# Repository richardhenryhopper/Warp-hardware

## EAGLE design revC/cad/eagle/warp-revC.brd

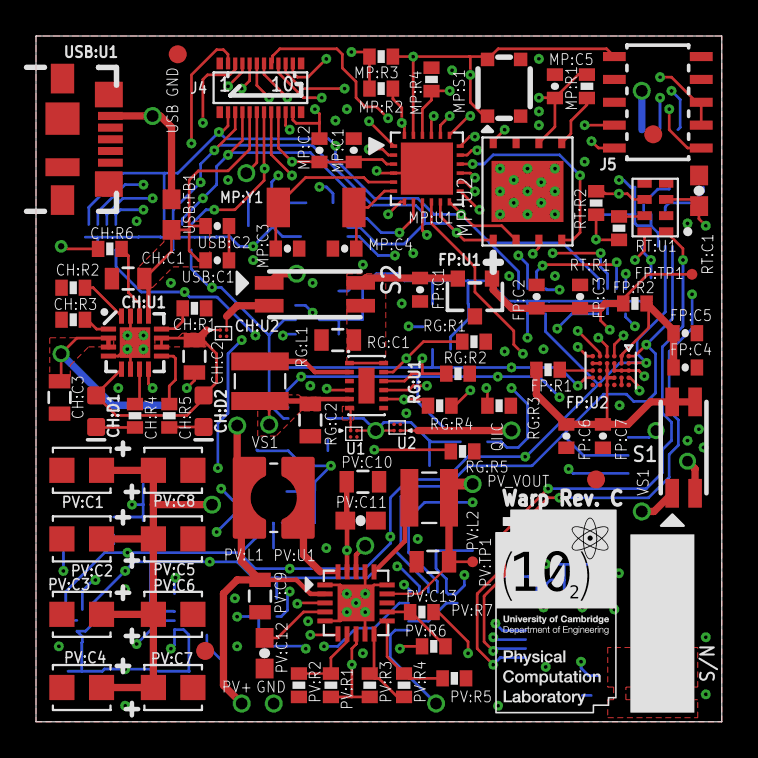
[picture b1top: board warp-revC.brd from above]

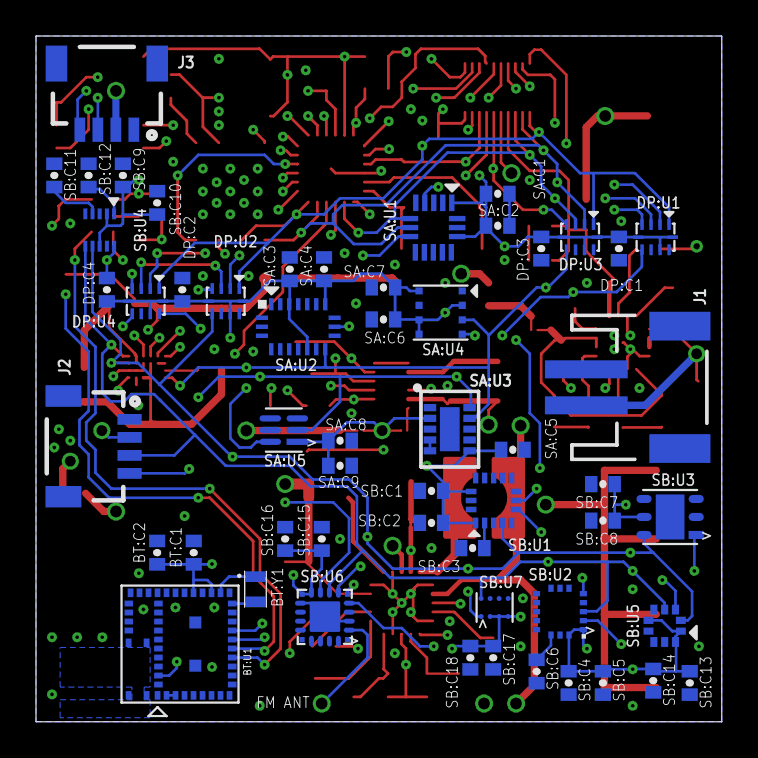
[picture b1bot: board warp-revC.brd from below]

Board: 10 copper layers, 38.1 x 38.1 mm, 143 parts (54 on the bottom side), 72 nets.

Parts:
BT:C1: 0.1uF; 0402-CAP
BT:C2: 1uF; 0402-CAP
BT:U1: BGX13S22GA-V21R; BGX13S
BT:Y1: IQXC-25
CH:C1: 1uF; 0805
CH:C2, CH:C3: 4.7uF; 0805
CH:D1, CH:D2: LED-0603
CH:R1: 2.94k; 0402-RES
CH:R2: 4.32k; 0402-RES
CH:R3: 10k; 0402-RES
CH:R4, CH:R5: 4.7k; 0402-RES
CH:R6: 56.2k; 0402-RES
CH:U1: BQ24230VQFN; PVQFN-N16
CH:U2: MAX40200; DSBGA
DP:C1, DP:C2, DP:C3, DP:C4: 0.1uF; 0402-CAP
DP:U1, DP:U2, DP:U3, DP:U4: ISL23415UTQFN; ISL23415
FD1, FD2, FD3, FD4: FIDUCIAL1X2; FIDUCIAL-1X2
FP:C1, FP:C2: 1uF; 0402-CAP
FP:C3, FP:C4, FP:C7: 0.1uF; 0402-CAP
FP:C5, FP:C6: 10uF; 0402-CAP
FP:R1: 10k; 0402-RES
FP:R2: 100; 0402-RES
FP:TP1: TPSTP06R; TP06R
FP:U1: MCP1811AT-012/TTSOT-23-3; SOT23-3
FP:U2: ICE40UP5K-UWG30; LATTICE-WLCSP-30
J1: JST-2-SMD
J2, J3: QIIC connector; 1X04_1MM_RA
J4: DF40FC-20DP-0.4V(51); DF40C-20DP-0.4V(51)
J5: CORTEX_DEBUG_SMD; SAMTECH_FTSH-105-01
MP:C1, MP:C5: 0.1uF; 0402-CAP
MP:C2: 4.7uF (pol); 0402-CAP
MP:C3, MP:C4: 33pF; 0402-CAP
MP:R1, MP:R2, MP:R4: 10k; 0402-RES
MP:R3: 4.7k; 0402-RES
MP:S1: EVPAYG0BAEVPAYG0BA; EVPAYG0BA
MP:U1: MKL03Z32VFK4RQFN24; MKL03Z32VFK4R
MP:U2: AT45DB641E-MHN-Y; UDFN
MP:Y1: CM519-SMD; CM519
PV:C1, PV:C2, PV:C3, PV:C4, PV:C5, PV:C6, PV:C7, PV:C8: CPX3225A7552D; CPX3225A752D
PV:C9, PV:C10: 4.7uF; 0805
PV:C11: 0.1uF; 0603-CAP
PV:C12: 10nF; 0603-CAP
PV:C13: 22uF; 0805
PV:L1: 22uH; WE-TPC_3816
PV:L2: 10uH; WE-TPC_2811/2813_OLD
PV:R1: 4.02M; 0402-RES
PV:R2: 9.09M; 0402-RES
PV:R3: 1.3M; 0402-RES
PV:R4: 5.36M; 0402-RES
PV:R5: 6.49M; 0402-RES
PV:R6: 8.87M; 0402-RES
PV:R7: 4.22M; 0402-RES
PV:TP1: TPSTP06R; TP06R
PV:U1: BQ25570PVQFN; BQ25570
RG:C1, RG:C2: 10uF; 0805
RG:L1: 2.2uH; WE-TPC_2828_OLD
RG:R1, RG:R2, RG:R3, RG:R4, RG:R5: 2M; 0402-RES
RG:U1: TPS6274XWSON; WSON-12
RT:C1: 0.1uF; 0603-CAP
RT:R1, RT:R2: 10k; 0402-RES
RT:U1: RV-8803-C7_RTC; RV-C7
S1, S2: CHS-02_SWITCH
SA:C1, SA:C3, SA:C6, SA:C8: 0.1uF; 0402-CAP
SA:C2, SA:C4, SA:C7, SA:C9: 1uF; 0402-CAP
SA:C5: 4.7uF; 0402-CAP
SA:U1: ADXL362
SA:U2: BMX055
SA:U3: CCS811; LGA10
SA:U4: BME680LGA; BME680
SA:U5: TCS34725FN; TCS3772
SB:C1, SB:C3, SB:C4, SB:C7, SB:C9, SB:C11, SB:C12, SB:C13, SB:C16, SB:C17: 0.1uF; 0402-CAP
SB:C2, SB:C8, SB:C10, SB:C18: 1uF; 0402-CAP
SB:C5: 10uF; 0402-CAP
SB:C6: 10nF (25V); 0402-CAP
SB:C14: 4.7uF; 0402-CAP
SB:C15: 22nF; 0402-CAP
SB:U1: MMA8451Q
SB:U2: L3GD20H
SB:U3: SI7021
SB:U4: MAG3110
SB:U5: LPS25H
SB:U6: SI4705
SB:U7: HDC1000
U1, U2: MAX40200; DSBGA
USB:C1: 4.7uF (pol); 0402-CAP
USB:C2: 0.1uF; 0402-CAP
USB:FB1: 600R/1A; 0603
USB:U1: MOLEX_USB_47346-0001MICRO_USB_B; USB-B-MICRO-SMD

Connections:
ADXL362_SPI_CS: MP:U1.P$15, SA:U1.P$8
BAT: CH:C3.1, CH:U1.2, CH:U1.3, J1.2
BGX13S_!RST: BT:U1.44, J4.P$7, MP:U1.P$7
BOOST_VBAT: PV:C1.+, PV:C2.+, PV:C3.+, PV:C4.+, PV:C5.+, PV:C6.+, PV:C7.+, PV:C8.+, PV:U1.18
BT:N$1: BT:U1.21, BT:Y1.1
BT:N$2: BT:U1.19, BT:Y1.2
BT:N$3: BT:U1.2, BT:U1.3
CH:BQ24230_OUT: CH:C2.1, CH:D1.A, CH:D2.A, CH:U1.5, CH:U1.10, CH:U1.11, CH:U2.A1
CH:N$1: CH:R2.2, CH:U1.16
CH:N$2: CH:R1.2, CH:U1.12
CH:N$3: CH:R4.1, CH:U1.7
CH:N$4: CH:R3.2, CH:U1.1
CH:N$5: CH:R5.1, CH:U1.9
CH:N$6: CH:D1.C, CH:R4.2
CH:N$7: CH:D2.C, CH:R5.2
CH:N$8: CH:R6.2, CH:U1.14
CHARGE_VOUT: CH:U2.A2, S2.2
CLK32K: MP:U1.P$21, SB:U6.P$9
FP:CRESET_B: FP:R1.1, FP:U2.F3
FP:ICE40_VCC_PLL: FP:C4.1, FP:C5.1, FP:R2.1, FP:U2.B1, FP:U2.B2
FP:VCC_1V2: FP:C2.1, FP:C3.1, FP:R2.2, FP:TP1.TP, FP:U1.1, FP:U2.A3, FP:U2.B3, FP:U2.C2, FP:U2.C3
FPGA_CS: FP:U2.C1, MP:U1.P$13
FPGA_VS: FP:C6.1, FP:C7.1, FP:R1.2, FP:U2.C4, FP:U2.D2, FP:U2.D3, FP:U2.D4, FP:U2.D5, S1.1', S1.2'
GND: BT:C1.2, BT:C2.2, BT:U1.1, BT:U1.4, BT:U1.5, BT:U1.20, BT:U1.31, BT:U1.45, BT:U1.46, BT:U1.47, BT:U1.48, BT:U1.49, BT:U1.50, BT:U1.51, CH:C1.2, CH:C2.2, CH:C3.2, CH:R1.1, CH:R2.1, CH:R3.1, CH:R6.1, CH:U1.4, CH:U1.6, CH:U1.8, CH:U1.15, CH:U1.EP, CH:U2.B2, DP:C1.2, DP:C2.2, DP:C3.2, DP:C4.2, DP:U1.9, DP:U2.9, DP:U3.9, DP:U4.9, FP:C1.2, FP:C2.2, FP:C3.2, FP:C4.2, FP:C5.2, FP:C6.2, FP:C7.2, FP:U1.3, FP:U2.B4, FP:U2.B5, FP:U2.E2, FP:U2.F2, J1.1, J2.1, J3.1, J4.P$20, J5.3, J5.5, MP:C1.2, MP:C2.2, MP:C3.2, MP:C4.2, MP:C5.2, MP:R4.2, MP:S1.B, MP:S1.B', MP:U1.P$4, MP:U1.P$PAD, MP:U2.7, MP:U2.9, PV:C1.-, PV:C2.-, PV:C3.-, PV:C4.-, PV:C5.-, PV:C6.-, PV:C7.-, PV:C8.-, PV:C9.2, PV:C10.2, PV:C11.2, PV:C12.2, PV:C13.2, PV:R2.1, PV:R5.1, PV:R7.1, PV:U1.1, PV:U1.5, PV:U1.9, PV:U1.15, PV:U1.17, PV:U1.21, RG:C1.2, RG:C2.2, RG:R1.1, RG:R2.1, RG:R3.1, RG:R4.1, RG:R5.1, RG:U1.3, RT:C1.2, RT:U1.4, RT:U1.5, SA:C1.2, SA:C2.2, SA:C3.2, SA:C4.2, SA:C5.2, SA:C6.2, SA:C7.2, SA:C8.2, SA:C9.2, SA:U1.P$12, SA:U1.P$13, SA:U1.P$16, SA:U2.P$4, SA:U2.P$6, SA:U2.P$12, SA:U2.P$17, SA:U2.P$20, SA:U3.1, SA:U3.7, SA:U3.EP, SA:U4.1, SA:U4.7, SA:U5.P$3, SB:C1.2, SB:C2.2, SB:C3.2, SB:C4.2, SB:C5.2, SB:C6.2, SB:C7.2, SB:C8.2, SB:C9.2, SB:C10.2, SB:C11.2, SB:C12.2, SB:C13.2, SB:C14.2, SB:C15.2, SB:C16.2, SB:C17.2, SB:C18.2, SB:U1.P$5, SB:U1.P$7, SB:U1.P$10, SB:U1.P$12, SB:U2.P$4, SB:U2.P$9, SB:U2.P$10, SB:U2.P$11, SB:U2.P$12, SB:U2.P$13, SB:U2.P$15, SB:U3.P$2, SB:U4.P$5, SB:U4.P$10, SB:U5.P$3, SB:U5.P$5, SB:U5.P$8, SB:U5.P$9, SB:U6.P$3, SB:U6.P$6, SB:U6.P$12, SB:U6.P$21, SB:U7.B2, U1.B2, U2.B2, USB:C1.2, USB:C2.2, USB:U1.GND, USB:U1.S1, USB:U1.S2, USB:U1.S3, USB:U1.S4, USB:U1.S5, USB:U1.S6
I2C0_SCL/UART_TX: BT:U1.14, J4.P$5, MP:U1.P$17, RT:U1.8
I2C0_SDA/UART_RX: BT:U1.13, J4.P$6, MP:U1.P$18, RT:U1.1
I2C1_SCL: DP:U1.6, FP:U2.A4, J3.4, J4.P$1, SA:U2.P$9, SA:U3.10, SA:U4.4, SA:U5.P$2
I2C1_SDA: DP:U3.6, FP:U2.F4, J3.3, J4.P$2, SA:U2.P$11, SA:U3.9, SA:U4.3, SA:U5.P$6
I2C2_SCL: DP:U2.6, FP:U2.A2, J2.4, J4.P$3, SB:U1.P$4, SB:U2.P$2, SB:U3.P$6, SB:U4.P$7, SB:U5.P$2, SB:U6.P$7, SB:U7.A1
I2C2_SDA: DP:U4.6, FP:U2.A1, J2.3, J4.P$4, SB:U1.P$6, SB:U2.P$3, SB:U3.P$1, SB:U4.P$6, SB:U5.P$4, SB:U6.P$8, SB:U7.A2
ISL23415_SPI_CS: DP:U1.4, DP:U2.4, DP:U3.4, DP:U4.4, J4.P$16, MP:U1.P$20
MP:AT45DB321F_SPI_CS: MP:U1.P$16, MP:U2.4
MP:EXTAL0: MP:C3.1, MP:U1.P$5, MP:Y1.P$1
MP:N$4: MP:R1.1, MP:U2.5
MP:XTAL0: MP:C4.1, MP:U1.P$6, MP:Y1.P$2
PV:LBOOST: PV:L1.2, PV:U1.20
PV:LBUCK: PV:L2.1, PV:U1.16
PV:OK_HYST: PV:R3.1, PV:R4.2, PV:U1.10
PV:OK_PROG: PV:R4.1, PV:R5.2, PV:U1.11
PV:VBAT_OV: PV:R1.1, PV:R2.2, PV:U1.7
PV:VOUT_SET: PV:R6.1, PV:R7.2, PV:U1.12
PV:VRDIV: PV:R1.2, PV:R3.2, PV:R6.2, PV:U1.8
PV:VREF_SAMP: PV:C12.1, PV:U1.4
PV:VSTOR: PV:C10.1, PV:C11.1, PV:U1.3, PV:U1.6, PV:U1.19
PV_VIN: J4.P$15, PV:C9.1, PV:L1.1, PV:U1.2
PV_VOUT: PV:C13.1, PV:L2.2, PV:TP1.TP, PV:U1.14, S2.1
REG_CTRL: MP:U1.P$19, RG:R5.2, RG:U1.4
REG_LOAD: RG:U1.6, U1.A1
REG_VIN: FP:C1.1, FP:U1.2, RG:C1.1, RG:U1.1, RG:U1.12, S2.1', S2.2'
REG_VSEL1: MP:U1.P$1, RG:R1.2, RG:U1.11
REG_VSEL2: MP:U1.P$2, RG:R2.2, RG:U1.10
REG_VSEL3: MP:U1.P$9, RG:R3.2, RG:U1.9
REG_VSEL4: MP:U1.P$10, RG:R4.2, RG:U1.8
RG:SW: RG:L1.1, RG:U1.2
RT:N$3: RT:R1.1, RT:U1.7
RTC_!INT!/RESET_B: J4.P$10, J5.10, MP:R3.1, MP:S1.A, MP:S1.A', MP:U1.P$23, RT:R2.1, RT:U1.6
SA:N$7: SA:U3.4, SA:U3.5
SB:CAP: SB:C6.1, SB:U2.P$14
SB:N$1: SB:C3.1, SB:U1.P$2
SB:N$2: SB:C11.1, SB:U4.P$4
SB:N$17: SB:C12.1, SB:U4.P$1
SI4705_!RST: J4.P$17, MP:U1.P$14, SB:U6.P$5
SPI_MISO/UART_RTS: BT:U1.16, DP:U1.2, DP:U2.2, DP:U3.2, DP:U4.2, FP:U2.F1, J4.P$12, MP:U1.P$11, MP:U2.1, SA:U1.P$7
SPI_MOSI/UART_CTS: BT:U1.15, DP:U1.3, DP:U2.3, DP:U3.3, DP:U4.3, FP:U2.E1, J4.P$13, MP:U1.P$8, MP:U2.8, SA:U1.P$6
SPI_SCK: DP:U1.1, DP:U2.1, DP:U3.1, DP:U4.1, FP:U2.D1, J4.P$11, MP:U1.P$12, MP:U2.2, SA:U1.P$4
SWD_CLK: J4.P$9, J5.4, MP:R4.1, MP:U1.P$22
SWD_DIO: J4.P$8, J5.2, MP:R2.1, MP:U1.P$24
USB:VBUS: USB:FB1.2, USB:U1.VBUS
USB_5V: CH:C1.1, CH:U1.13, J4.P$14, USB:C1.1, USB:C2.1, USB:FB1.1
VCC_QIIC: J2.2, J3.2, U2.A1
VS1: J4.P$18, J5.1, MP:C1.1, MP:C2.1, MP:C5.1, MP:R1.2, MP:R2.2, MP:R3.2, MP:U1.P$3, MP:U2.3, MP:U2.6, RG:C2.1, RG:L1.2, RG:U1.5, RT:C1.1, RT:R1.2, RT:R2.2, RT:U1.3, S1.1
VS2: BT:C1.1, BT:C2.1, BT:U1.22, BT:U1.24, DP:C1.1, DP:C2.1, DP:C3.1, DP:C4.1, DP:U1.5, DP:U1.8, DP:U1.10, DP:U2.5, DP:U2.8, DP:U2.10, DP:U3.5, DP:U3.8, DP:U3.10, DP:U4.5, DP:U4.8, DP:U4.10, J4.P$19, S1.2, SA:C1.1, SA:C2.1, SA:C3.1, SA:C4.1, SA:C5.1, SA:C6.1, SA:C7.1, SA:C8.1, SA:C9.1, SA:U1.P$1, SA:U1.P$14, SA:U2.P$3, SA:U2.P$7, SA:U2.P$13, SA:U3.2, SA:U3.6, SA:U4.2, SA:U4.5, SA:U4.6, SA:U4.8, SA:U5.P$1, SB:C1.1, SB:C2.1, SB:C4.1, SB:C5.1, SB:C7.1, SB:C8.1, SB:C9.1, SB:C10.1, SB:C13.1, SB:C14.1, SB:C15.1, SB:C16.1, SB:C17.1, SB:C18.1, SB:U1.P$1, SB:U1.P$14, SB:U2.P$1, SB:U2.P$5, SB:U2.P$16, SB:U3.P$5, SB:U4.P$2, SB:U4.P$8, SB:U5.P$1, SB:U5.P$6, SB:U5.P$10, SB:U6.P$10, SB:U6.P$11, SB:U7.B1, SB:U7.C1, SB:U7.D1, U1.A2, U2.A2

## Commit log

2019-11-08 Rerouted FPGA

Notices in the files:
parts and their libraries:
SparkFun-Passives: Licensing: Creative Commons ShareAlike 4.0 International - https://creativecommons.org/licenses/by-sa/4.0
EMCComponents: Copyright: Würth Elektronik
